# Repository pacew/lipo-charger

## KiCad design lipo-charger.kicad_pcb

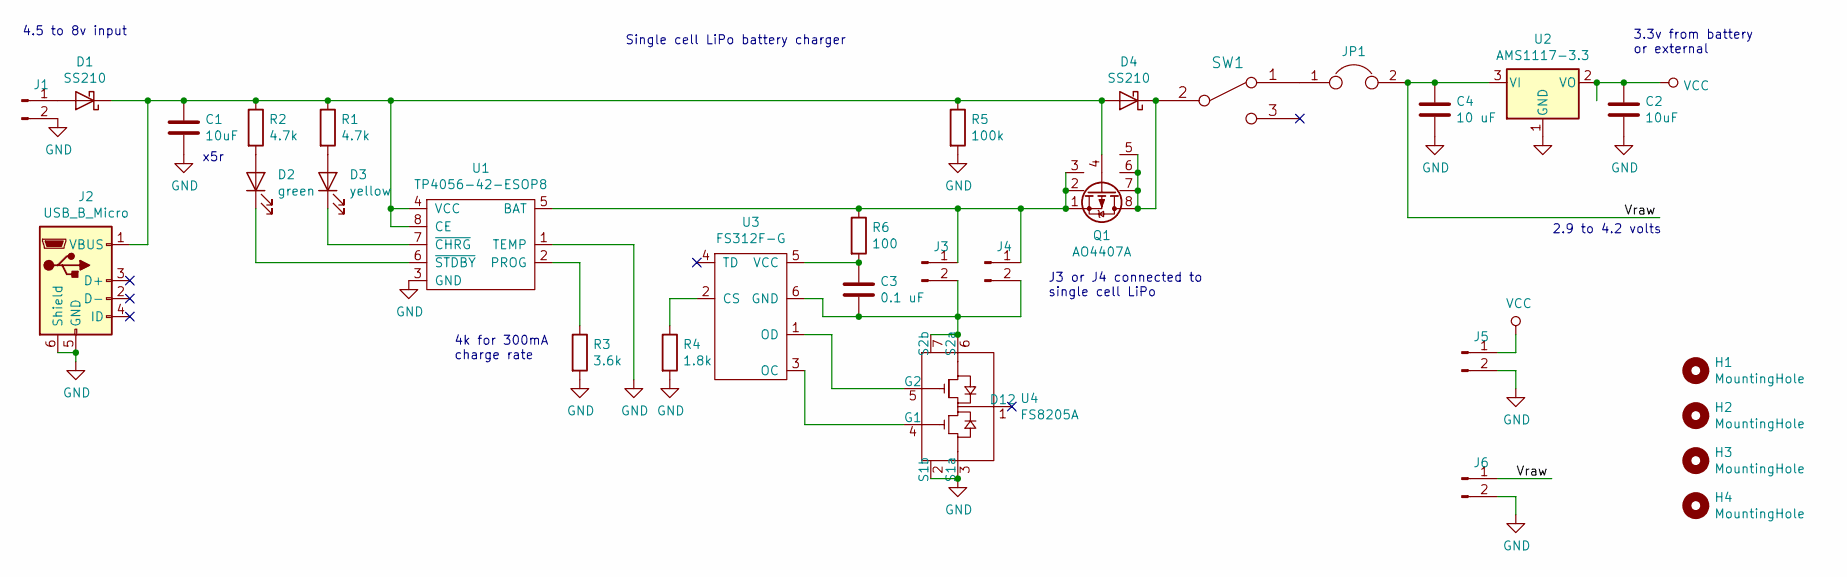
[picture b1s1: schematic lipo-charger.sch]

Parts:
C1, C2: 10uF; C_0805_2012Metric
C3: 0.1 uF; C_0805_2012Metric
C4: 10 uF; C_0805_2012Metric
D1, D4: SS210; D_MELF
D2: green; LED_0805_2012Metric
D3: yellow; LED_0805_2012Metric
H1, H2, H3, H4: MountingHole; MountingHole_3.2mm_M3
J1, J4, J5, J6: Conn_01x02_Male; PinHeader_1x02_P2.54mm_Vertical
J2: USB_B_Micro; USB_Micro-B_Molex-105017-0001
J3: Conn_01x02_Male; JST_PH_B2B-PH-K_1x02_P2.00mm_Vertical
JP1: Jumper; PinHeader_1x02_P2.54mm_Vertical
Q1: AO4407A; SOIC-8_3.9x4.9mm_P1.27mm
R1, R2: 4.7k; R_0805_2012Metric
R3: 3.6k; R_0805_2012Metric
R4: 1.8k; R_0805_2012Metric
R5: 100k; R_0805_2012Metric
R6: 100; R_0805_2012Metric
SW1: SWITCH_SPDT; Switch_Toggle_ATE1D-2M3-10-Z
U1: TP4056-42-ESOP8; SOP-8_3.9x4.9mm_P1.27mm
U2: AMS1117-3.3; SOT-223-3_TabPin2
U3: FS312F-G; SOT-23-6
U4: FS8205A; TSSOP-8_4.4x3mm_P0.65mm

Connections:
/Vraw: C4.1, J6.1, JP1.2, U2.3 (VI)
GND: C1.2, C2.2, C4.2, J1.2, J2.5 (GND), J2.6 (Shield), J5.2, J6.2, R3.2, R4.2, R5.2, U1.1 (TEMP), U1.3 (GND), U2.1 (GND), U4.2 (S1b), U4.3 (S1a)
unnamed: C1.1, D1.1 (K), D4.2 (A), J2.1 (VBUS), Q1.4 (G), R1.1, R2.1, R5.1, U1.4 (VCC), U1.8 (CE)
unnamed: C3.1, R6.2, U3.5 (VCC)
unnamed: C3.2, J3.2, J4.2, U3.6 (GND), U4.6 (S2a), U4.7 (S2b)
unnamed: D1.2 (A), J1.1
unnamed: D2.1 (K), U1.6 (~STDBY)
unnamed: D2.2 (A), R2.2
unnamed: D3.1 (K), U1.7 (~CHRG)
unnamed: D3.2 (A), R1.2
unnamed: D4.1 (K), Q1.5 (Dd), Q1.6 (Dc), Q1.7 (Db), Q1.8 (D), SW1.2
unnamed: J3.1, J4.1, Q1.1 (S), Q1.2 (Sb), Q1.3 (Sc), R6.1, U1.5 (BAT)
unnamed: JP1.1, SW1.1
unnamed: R3.1, U1.2 (PROG)
unnamed: R4.1, U3.2 (CS)
unnamed: U3.1 (OD), U4.5 (G2)
unnamed: U3.3 (OC), U4.4 (G1)
VCC: C2.1, J5.1, U2.2 (VO)

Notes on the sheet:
x5r
4k for 300mA charge rate
J3 or J4 connected to single cell LiPo
4.5 to 8v input
3.3v from battery or external
Single cell LiPo battery charger
2.9 to 4.2 volts

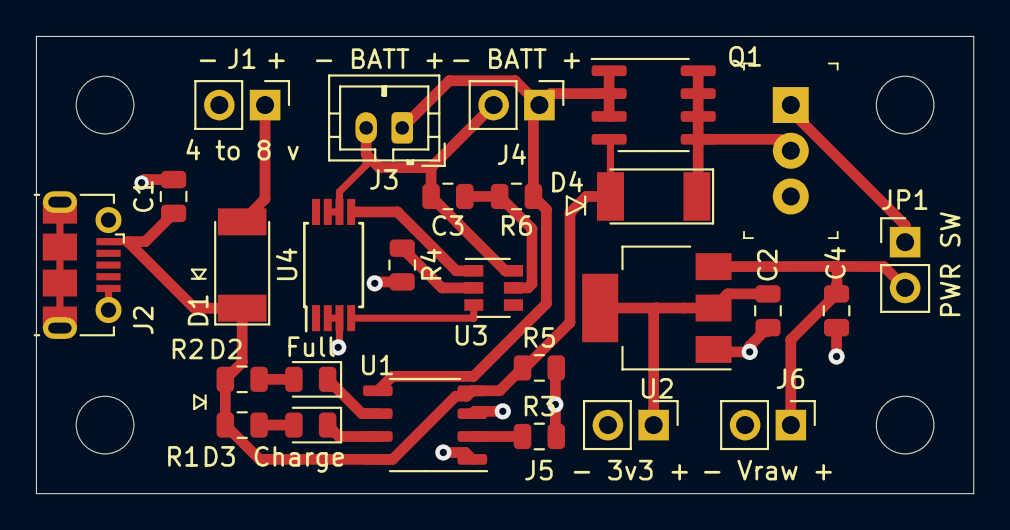
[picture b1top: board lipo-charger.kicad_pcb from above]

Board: 2 copper layers, 52.1 x 25.4 mm, 31 parts (0 on the bottom side), 18 nets.

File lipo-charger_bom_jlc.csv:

"Comment","Designator","Footprint","LCSC Part #"
"10uF","C1,C2","C_0805_2012Metric","C15850"
"0.1 uF","C3","C_0805_2012Metric","C1710"
"10 uF","C4","C_0805_2012Metric","C15850"
"SS210","D1,D4","D_MELF","C14996"
"green","D2","LED_0805_2012Metric","C2297"
"yellow","D3","LED_0805_2012Metric","C2296"
"AO4407A","Q1","SOIC-8_3.9x4.9mm_P1.27mm","C16072"
"4.7k","R2,R1","R_0805_2012Metric","C17673"
"3.6k","R3","R_0805_2012Metric","C18359"
"1.8k","R4","R_0805_2012Metric","C17398"
"100k","R5","R_0805_2012Metric","C17407"
"100","R6","R_0805_2012Metric","C17408"
"TP4056-42-ESOP8","U1","SOP-8_3.9x4.9mm_P1.27mm","C16581"
"AMS1117-3.3","U2","SOT-223-3_TabPin2","C6186"
"FS312F-G","U3","SOT-23-6","C14213"
"FS8205A","U4","TSSOP-8_4.4x3mm_P0.65mm","C16052"

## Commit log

2020-07-25 start
2020-07-25 notes
2020-07-26 jlc ordered
2020-08-05 docs
